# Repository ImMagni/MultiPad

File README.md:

# MultiPad
<br>
## Why
I wanted to create a multipad for gaming and other tasks. When the kit arrives, I might add more modes like editing and streaming.
## Challenges
It was very difficult because this was my first project. I only knew how to program, but I didn’t know how to make models,and pcbs, i literally had to redoing the pcb seven times.
## BOM
- 1x XIAO RP2040
- 9x 1N4148 diodes
- 8x Cherry MX Switches
- 8x Blank DSA Keycaps
- 1x EC11 Rotary encoder
- 1x 0.91 inch OLED display
- 4x M3 Heatsets
- 4x M3x16 screws
  
Case|Schematic|Pcb
:-:|:-:|:-:|
|| 

-|-
:-:|:-:|
|

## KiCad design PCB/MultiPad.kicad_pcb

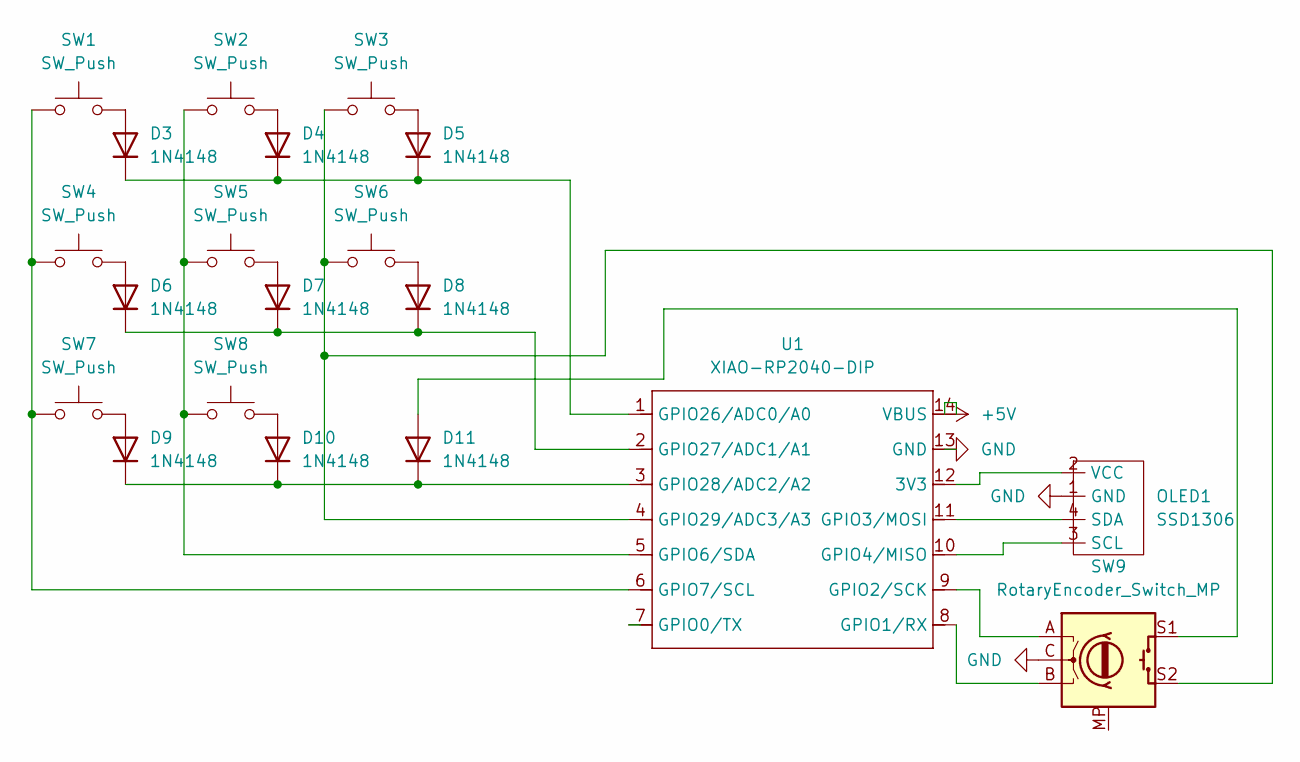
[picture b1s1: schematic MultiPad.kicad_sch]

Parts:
D3, D4, D5, D6, D7, D8, D9, D10, D11: 1N4148; D_DO-35_SOD27_P7.62mm_Horizontal
OLED1: SSD1306; SSD1306-0.91-OLED-4pin-128x32
SW1, SW2, SW3, SW4, SW5, SW6, SW7, SW8: SW_Push; SW_Cherry_MX_1.00u_PCB
SW9: RotaryEncoder_Switch_MP; RotaryEncoder_Alps_EC11E-Switch_Vertical_H20mm
U1: XIAO-RP2040-DIP

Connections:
+5V: U1.14 (VBUS)
GND: OLED1.1 (GND), SW9.C, U1.13 (GND)
unnamed: D3.2 (A), SW1.2
unnamed: D3.1 (K), D4.1 (K), D5.1 (K), U1.1 (GPIO26/ADC0/A0)
unnamed: D4.2 (A), SW2.2
unnamed: D5.2 (A), SW3.2
unnamed: D6.2 (A), SW4.2
unnamed: D6.1 (K), D7.1 (K), D8.1 (K), U1.2 (GPIO27/ADC1/A1)
unnamed: D7.2 (A), SW5.2
unnamed: D8.2 (A), SW6.2
unnamed: D9.2 (A), SW7.2
unnamed: D10.2 (A), SW8.2
unnamed: D9.1 (K), D10.1 (K), D11.1 (K), U1.3 (GPIO28/ADC2/A2)
unnamed: D11.2 (A), SW9.S1
unnamed: OLED1.3 (SCL), U1.10 (GPIO4/MISO)
unnamed: OLED1.4 (SDA), U1.11 (GPIO3/MOSI)
unnamed: OLED1.2 (VCC), U1.12 (3V3)
unnamed: SW9.B, U1.8 (GPIO1/RX)
unnamed: SW9.A, U1.9 (GPIO2/SCK)
unnamed: SW2.1, SW5.1, SW8.1, U1.5 (GPIO6/SDA)
unnamed: SW1.1, SW4.1, SW7.1, U1.6 (GPIO7/SCL)
unnamed: SW3.1, SW6.1, SW9.S2, U1.4 (GPIO29/ADC3/A3)

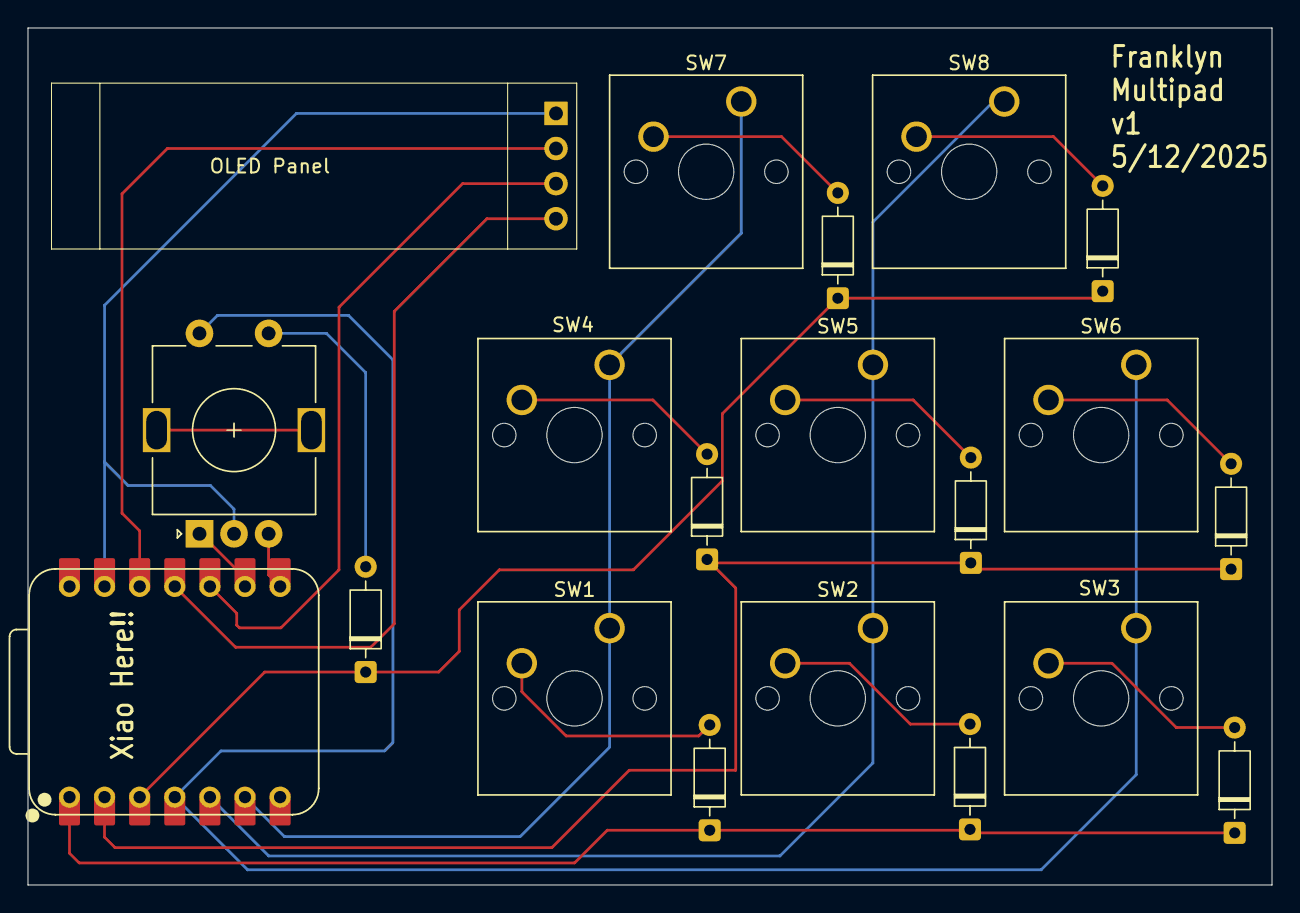
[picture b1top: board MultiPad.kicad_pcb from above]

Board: 2 copper layers, 90.0 x 62.0 mm, 20 parts (0 on the bottom side), 21 nets.

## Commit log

2025-12-06 Actualizar README.md
